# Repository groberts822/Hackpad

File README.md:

The Design of my hackpad/macropad

The CAD models of the top and bottom parts of the case

This is the Schematic

This is the PCB
Note: SMD instead of DIP does not matter to me. If it ends up being to hard to solder, the kits (or I also have either way) come with the header pins to do it DIP instead of straight SMD, but I tend to prefer SMD even with the slight challenge.

3D Model w/ all parts of PCB

Final/Physical Build!!

Final Build Demo

https://www.youtube.com/watch?v=0jgFtQDJzT8 

Bill of Materials (Also provided as a file in .csv format)

Item,Order Qty,Actual Usage:
- Seeed XIAO RP2040,1,1
- MX Mechanical Switches,1 Pack (36),6
- DSA Keycaps (1u),1 Pack (24),6
- 1N4148 Diodes,1 Pack (150),6
- EC11 Rotary Encoder,1 Pack (6),1
- "0.91"" OLED Display",1 Pack (5),1

----------------
The hackpad, or at least my customized version of it, contains 6 keys, a rotary encoder (knob), and a small OLED display. I plan to utilize this macropad for tasks including gaming, productivity shortcuts, and for general assist in tasks including school work, 3D modelling, and so on.
I chose this project as I wanted to challenge myself, especially since this is my first time designing a PCB, or at least my first successful PCB design. I found it very challenging through tasks like the PCB 3D model and including all the proper electronics when some required deep internet browsing. I am quite familiar with 3D modelling already, but I enjoy the process of being able to combine the new skill--designing PCBs--with my existing skills--like 3D modelling.
The way this macropad will work is through the XIAO RP2040's USB-C port, where the firmware will be flashed and each key will serve a task--like a shortcut to open Spotify--and the rotary encoder will serve as a volume control knob.

The images associated with this project are organized into different folders. Beginning to navigate the folders, you will see a "Case", "Case & PCB", and "PCB" folders, as well as this README page, and the Bill of Materials (BOM). Put simply, the "Case" folder contains a single STEP file, being of the 3D printed case itself. Inside the "PCB" folder, contains an image of the Schematic, PCB layout, a 3D generated model of the PCB, a STEP file model of the PCB itself, and another folder--containing all files necessary for ordering the PCB and for reopening the design on KiCad. Lastly, navigating on over to the "Case & PCB" folder, it contains 3 images--one of the fully assembled design but at an Orthographic view, while another image contains that same assembled design, but a top-down view, and the last image being an exploded view of the design. Alongside the images is another STEP file, and a f3z file (Fusion360 archived file), and both of these files contain the same fully assembled 3D model, just in different file formats (mentioned on Submission guidelines page)

The firmware/code file, named as "main.py", is a simple macropad setup for now, the keys are bind to buttons F13-F18, which are able to be bind using apps like AutoHotkey to control whatever I like. The code uses the rotary encoder knob to act as a simple volume control knob, and the OLED displays simple startup text for now--"Hackpad Ready"--and once volume is changed, it will momentarily display "Volume: XX" with XX being the volume on a 0-100 scale.

Thanks for checking out my macropad/hackpad!

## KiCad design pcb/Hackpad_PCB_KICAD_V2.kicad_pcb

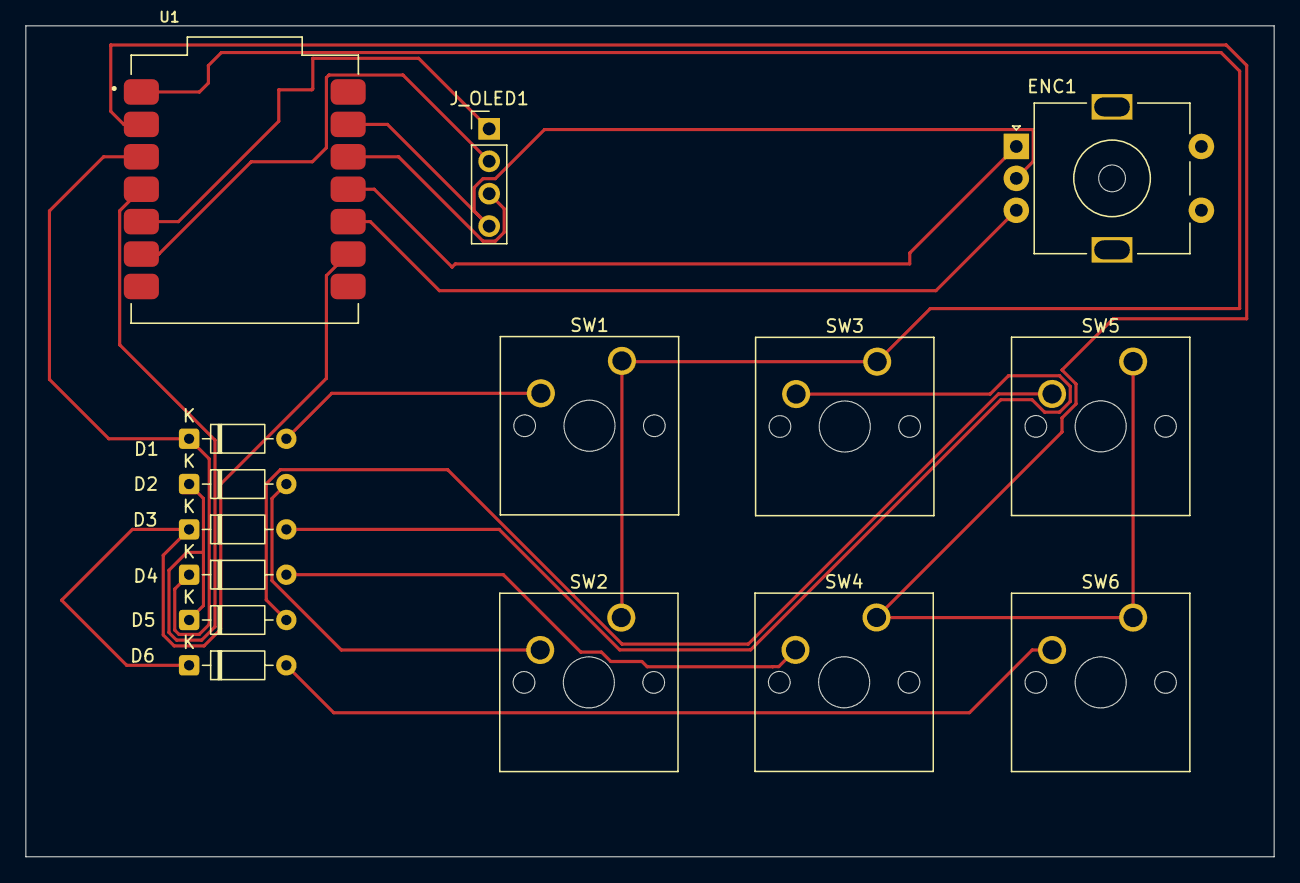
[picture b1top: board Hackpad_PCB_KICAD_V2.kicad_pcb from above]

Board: 2 copper layers, 97.8 x 65.1 mm, 15 parts (0 on the bottom side), 17 nets.

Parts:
D1, D2, D3, D4, D5, D6: 1N4148; D_DO-35_SOD27_P7.62mm_Horizontal
ENC1: RotaryEncoder; RotaryEncoder_Alps_EC11E-Switch_Vertical_H20mm_MountingHoles
J_OLED1: Conn_01x04; PinHeader_1x04_P2.54mm_Vertical
SW1, SW2, SW3, SW4, SW5, SW6: SW_Push; SW_Cherry_MX_1.00u_PCB
U1: XIAO-RP2040-DIP; XIAORF2040

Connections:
/3V3: J_OLED1.3, U1.12 (3V3)
/C0: D1.1 (K), D4.1 (K), U1.3 (GPIO28/ADC2/A2)
/C1: D2.1 (K), D5.1 (K), U1.4 (GPIO29/ADC3/A3)
/C2: D3.1 (K), D6.1 (K), U1.9 (GPIO2/SCK)
/ENC_A: ENC1.A, U1.11 (GPIO3/MOSI)
/ENC_B: ENC1.B, U1.10 (GPIO4/MISO)
/R0: SW1.1, SW2.1, SW3.1, U1.1 (GPIO26/ADC0/A0)
/R1: SW4.1, SW5.1, SW6.1, U1.2 (GPIO27/ADC1/A1)
/SCL: J_OLED1.2, U1.6 (GPIO7/SCL)
/SDA: J_OLED1.1, U1.5 (GPIO6/SDA)
GND: ENC1.C, J_OLED1.4, U1.13 (GND)
unnamed: D1.2 (A), SW1.2
unnamed: D2.2 (A), SW2.2
unnamed: D3.2 (A), SW3.2
unnamed: D4.2 (A), SW4.2
unnamed: D5.2 (A), SW5.2
unnamed: D6.2 (A), SW6.2

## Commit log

2026-02-11 Create 1
2026-02-11 Create cad
